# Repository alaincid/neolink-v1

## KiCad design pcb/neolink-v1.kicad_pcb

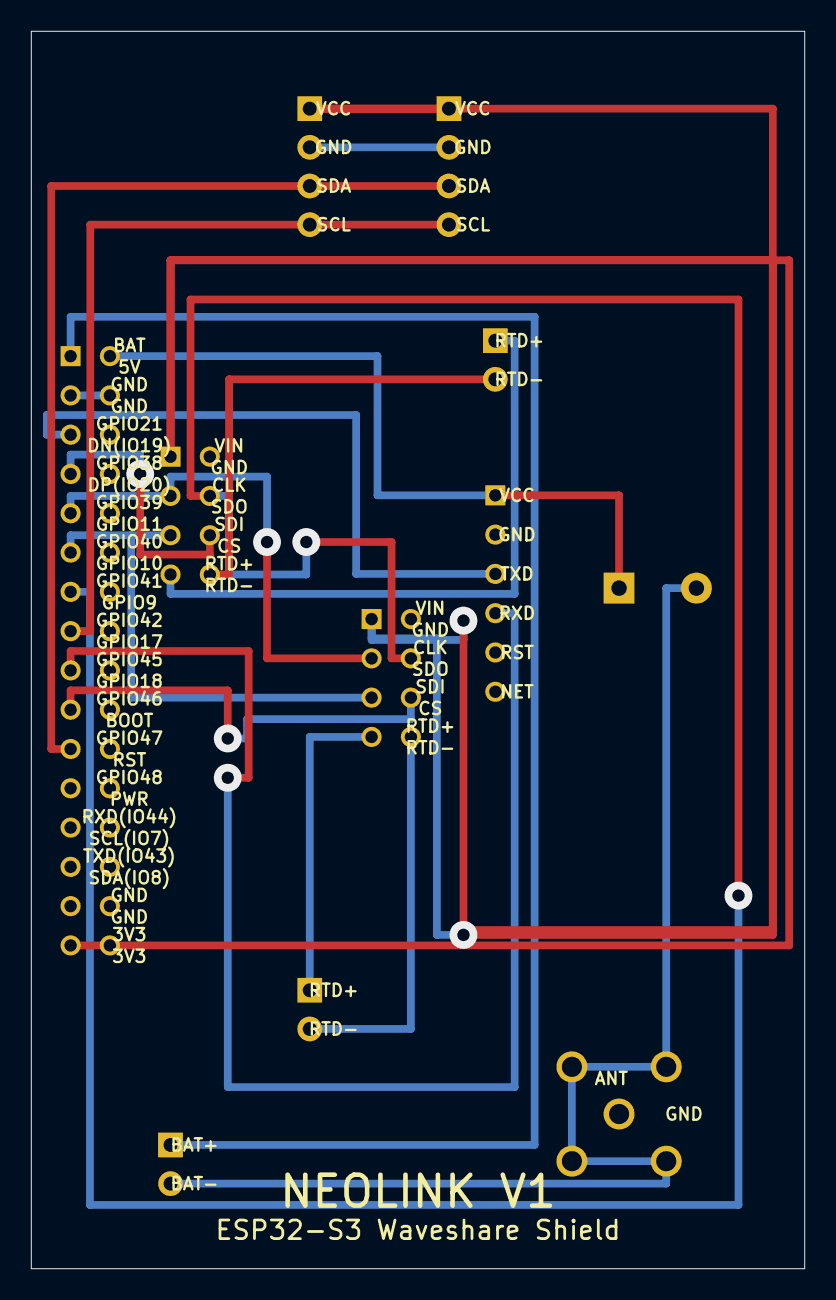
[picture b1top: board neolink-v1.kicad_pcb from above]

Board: 2 copper layers, 50.0 x 80.0 mm, 11 parts (0 on the bottom side), 17 nets.

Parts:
C1: 1000uF_10V; CP_Radial_D10.0mm_P5.00mm
J1: ESP32_2x16; PinHeader_2x16_P2.54mm_Vertical
J2: SIM800L_1x6; PinHeader_1x06_P2.54mm_Vertical
J3: MAX31865_1; PinHeader_2x04_P2.54mm_Vertical
J4: MAX31865_2; PinHeader_2x04_P2.54mm_Vertical
J5: SHT35_1; JST_XH_B4B-XH-A_1x04_P2.50mm_Vertical
J6: SHT35_2; JST_XH_B4B-XH-A_1x04_P2.50mm_Vertical
J7: PT100_1; JST_XH_B2B-XH-A_1x02_P2.50mm_Vertical
J8: PT100_2; JST_XH_B2B-XH-A_1x02_P2.50mm_Vertical
J9: LiPo; JST_XH_B2B-XH-A_1x02_P2.50mm_Vertical
J10: ANT_GSM; SMA_Molex_73251-1153_Vertical

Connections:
BAT: J1.1, J9.1
CLK_SPI: J1.9, J3.3, J4.3
CS_MAX1: J1.7, J3.6
CS_MAX2: J1.19, J4.6
GND: C1.2, J1.3, J1.4, J1.29, J1.30, J2.2, J3.2, J4.2, J5.2, J6.2, J9.2, J10.2, J10.3, J10.4, J10.5
I2C_SCL: J1.15, J5.4, J6.4
I2C_SDA: J1.21, J5.3, J6.3
MISO_SPI: J1.13, J3.4, J4.4
MOSI_SPI: J1.11, J3.5, J4.5
RTD1_N: J3.8, J7.2
RTD1_P: J3.7, J7.1
RTD2_N: J4.8, J8.2
RTD2_P: J4.7, J8.1
RXD_SIM: J1.17, J2.4
TXD_SIM: J1.5, J2.3
~VCC_3V3: J1.31, J1.32, J3.1, J4.1, J5.1, J6.1
~VCC_5V: C1.1, J1.2, J2.1

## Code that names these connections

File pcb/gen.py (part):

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# ESP32-S3 Waveshare Touch LCD 3.5 — exact firmware-verified pinout
# Left column = odd pins (1,3,5…31), right column = even pins (2,4,6…32)
ESP32_PINS = [
    "BAT",           "~{VCC_5V}",    # row 0   pins 1,2   BAT / 5V
    "GND",           "GND",          # row 1   pins 3,4   GND / GND
    "TXD_SIM",       "NC",           # row 2   pins 5,6   GPIO21→SIM_RX / NC
    "CS_MAX1",       "NC",           # row 3   pins 7,8   GPIO38→CS1    / NC
    "CLK_SPI",       "NC",           # row 4   pins 9,10  GPIO39→CLK    / NC
    "MOSI_SPI",      "NC",           # row 5   pins 11,12 GPIO40→MOSI   / NC
    "MISO_SPI",      "NC",           # row 6   pins 13,14 GPIO41→MISO   / NC
    "I2C_SCL",       "NC",           # row 7   pins 15,16 GPIO42→SCL    / NC
    "RXD_SIM",       "NC",           # row 8   pins 17,18 GPIO45→SIM_TX / NC
    "CS_MAX2",       "NC",           # row 9   pins 19,20 GPIO46→CS2    / NC
    "I2C_SDA",       "NC",           # row 10  pins 21,22 GPIO47→SDA    / NC
    "NC",            "NC",           # row 11  pins 23,24 GPIO48 / PWR
    "NC",            "NC",           # row 12  pins 25,26 RXD44  / SCL7
    "NC",            "NC",           # row 13  pins 27,28 TXD43  / SDA8
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    "3V3",           "3V3",          # row 15
]

SIM800L_PINS    = ["~{VCC_5V}", "GND", "TXD_SIM", "RXD_SIM", "RST_SIM", "PWR_SIM"]
MAX31865_1_PINS = ["~{VCC_3V3}", "GND", "CLK_SPI", "MISO_SPI",
                   "MOSI_SPI", "CS_MAX1", "RTD1_P", "RTD1_N"]
MAX31865_2_PINS = ["~{VCC_3V3}", "GND", "CLK_SPI", "MISO_SPI",
                   "MOSI_SPI", "CS_MAX2", "RTD2_P", "RTD2_N"]
SHT35_1_PINS    = ["~{VCC_3V3}", "GND", "I2C_SDA", "I2C_SCL"]
SHT35_2_PINS    = ["~{VCC_3V3}", "GND", "I2C_SDA", "I2C_SCL"]
PT100_1_PINS    = ["RTD1_P", "RTD1_N"]
PT100_2_PINS    = ["RTD2_P", "RTD2_N"]
LIPO_PINS       = ["BAT", "GND"]
SMA_PINS        = ["ANT_GSM", "GND"]

LIB_SYMS  = "(lib_symbols\n"
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FP_J8  = fp_jst("J8",  "PT100_2",     *POS['J8'],   2, PT100_2_PINS,
                labels=["RTD+","RTD-"])
FP_J9  = fp_jst("J9",  "LiPo",        *POS['J9'],   2, LIPO_PINS,
                labels=["BAT+","BAT-"])
FP_J10 = fp_sma("J10", "ANT_GSM",     *POS['J10'])
FP_C1  = fp_cap("C1",  "1000uF_10V",  *POS['C1'])

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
